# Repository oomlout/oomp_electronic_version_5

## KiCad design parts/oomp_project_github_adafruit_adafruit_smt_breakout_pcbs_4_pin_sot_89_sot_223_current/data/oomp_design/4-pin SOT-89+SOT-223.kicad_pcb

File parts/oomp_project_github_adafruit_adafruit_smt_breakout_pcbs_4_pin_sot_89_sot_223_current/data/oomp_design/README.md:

# OOMP KiCad design copy

Open `4-pin SOT-89+SOT-223.kicad_pro` (or the `.kicad_pcb` / `.kicad_sch`) in KiCad. Local OOMP libraries are under `libraries/`. Original inputs are preserved in [../original/](../original/).

Only verified unchanged installed KiCad defaults were renamed. Modified, custom, unmatched and unavailable items remain unchanged. Soldering variants are never swapped during conversion. Existing pad coordinates, nets and UUIDs are preserved.

See [conversion_report.yaml](conversion_report.yaml) for every conversion and skip. Copy this directory before editing; regeneration refuses to overwrite edited design files.

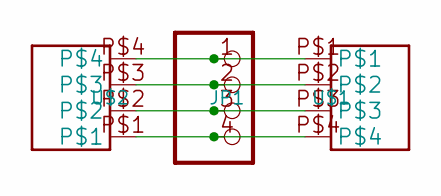
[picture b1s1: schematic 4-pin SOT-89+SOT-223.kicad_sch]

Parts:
JP1: PADS-4
U$1: SOT89
U$2: SOT223

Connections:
unnamed: JP1.1, U$1.P$1, U$2.P$4
unnamed: JP1.2, U$1.P$2, U$2.P$3
unnamed: JP1.3, U$1.P$3, U$2.P$2
unnamed: JP1.4, U$1.P$4, U$2.P$1

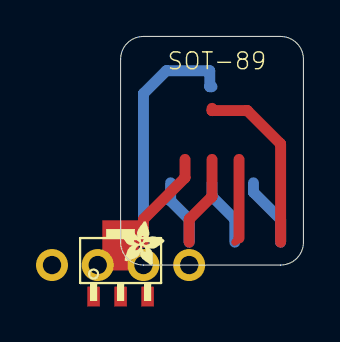
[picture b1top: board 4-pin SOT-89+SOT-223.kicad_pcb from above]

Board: 2 copper layers, 10.2 x 12.7 mm, 4 parts (1 on the bottom side), 4 nets.

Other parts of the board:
U$3: ADAFRUIT_2.5MM

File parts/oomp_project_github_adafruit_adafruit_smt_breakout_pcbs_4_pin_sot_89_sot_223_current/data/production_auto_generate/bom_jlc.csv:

Comment,Designator,Footprint,LCSC Part #
,U$3,4-pin SOT-89+SOT-223-import-fps:ADAFRUIT_2.5MM,
,JP1,4-pin SOT-89+SOT-223-import-fps:PADS-4,
SOT223,U$2,4-pin SOT-89+SOT-223-import-fps:SOT223,
SOT89,U$1,4-pin SOT-89+SOT-223-import-fps:SOT89,

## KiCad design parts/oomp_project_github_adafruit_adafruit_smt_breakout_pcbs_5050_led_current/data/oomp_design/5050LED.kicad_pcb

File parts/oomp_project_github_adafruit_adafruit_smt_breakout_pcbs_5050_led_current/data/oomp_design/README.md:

# OOMP KiCad design copy

Open `5050LED.kicad_pro` (or the `.kicad_pcb` / `.kicad_sch`) in KiCad. Local OOMP libraries are under `libraries/`. Original inputs are preserved in [../original/](../original/).

Only verified unchanged installed KiCad defaults were renamed. Modified, custom, unmatched and unavailable items remain unchanged. Soldering variants are never swapped during conversion. Existing pad coordinates, nets and UUIDs are preserved.

See [conversion_report.yaml](conversion_report.yaml) for every conversion and skip. Copy this directory before editing; regeneration refuses to overwrite edited design files.

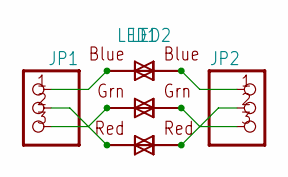
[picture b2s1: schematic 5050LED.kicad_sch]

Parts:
JP1, JP2: PINHD-1X3CB; 1X03-CLEANBIG
LED1, LED2: RGBLED5050

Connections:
unnamed: JP1.1, LED1.3 (BLUE_A), LED2.4 (BLUE_C)
unnamed: JP1.2, LED1.2 (RED_A), LED2.5 (RED_C)
unnamed: JP1.3, LED1.1 (GREEN_A), LED2.6 (GREEN_C)
unnamed: JP2.1, LED1.4 (BLUE_C), LED2.3 (BLUE_A)
unnamed: JP2.2, LED1.5 (RED_C), LED2.2 (RED_A)
unnamed: JP2.3, LED1.6 (GREEN_C), LED2.1 (GREEN_A)

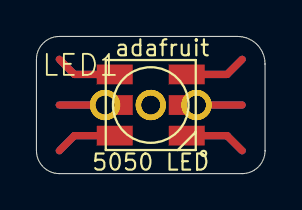
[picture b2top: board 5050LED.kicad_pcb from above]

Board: 2 copper layers, 12.7 x 7.6 mm, 4 parts (1 on the bottom side), 6 nets.

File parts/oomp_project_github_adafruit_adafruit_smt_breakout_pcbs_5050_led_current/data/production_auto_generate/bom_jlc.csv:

Comment,Designator,Footprint,LCSC Part #
,"JP1,JP2",5050LED-import-fps:1X03-CLEANBIG,C49257
RGBLED5050,"LED1,LED2",5050LED-import-fps:RGBLED5050,

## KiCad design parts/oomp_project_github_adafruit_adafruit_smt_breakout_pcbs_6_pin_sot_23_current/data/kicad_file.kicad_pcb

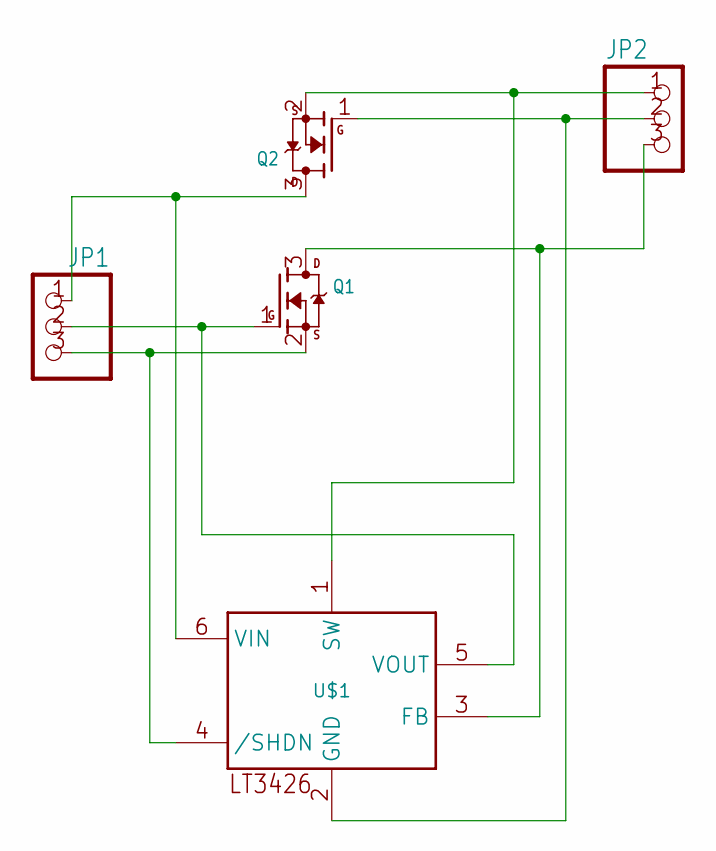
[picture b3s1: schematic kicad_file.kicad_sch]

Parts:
JP1, JP2: PINHD-1X3CB; 1X03-CLEANBIG
Q1, Q2: MOSFET-NREFLOW; SOT23
U$1: LT3426; SOT23-6

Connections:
GND: JP2.2, Q2.1 (G), U$1.2 (GND)
unnamed: JP2.3, Q1.3 (D), U$1.3 (FB)
unnamed: JP1.2, Q1.1 (G), U$1.5 (VOUT)
unnamed: JP1.3, Q1.2 (S), U$1.4 (/SHDN)
unnamed: JP2.1, Q2.2 (S), U$1.1 (SW)
unnamed: JP1.1, Q2.3 (D), U$1.6 (VIN)

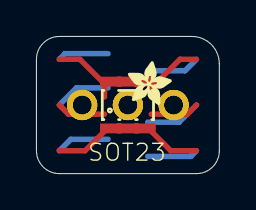
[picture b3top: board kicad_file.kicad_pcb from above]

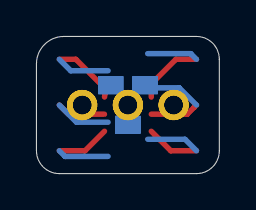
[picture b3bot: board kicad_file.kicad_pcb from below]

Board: 2 copper layers, 10.2 x 7.6 mm, 6 parts (2 on the bottom side), 6 nets.

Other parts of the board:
U$2: ADAFRUIT_2.5MM

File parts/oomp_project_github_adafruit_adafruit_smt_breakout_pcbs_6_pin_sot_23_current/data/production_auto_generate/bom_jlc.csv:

Comment,Designator,Footprint,LCSC Part #
,"JP1,JP2",6-pin SOT-23-import-fps:1X03-CLEANBIG,C49257
,U$2,6-pin SOT-23-import-fps:ADAFRUIT_2.5MM,
,"Q1,Q2",6-pin SOT-23-import-fps:SOT23,
LT3426,U$1,6-pin SOT-23-import-fps:SOT23-6,

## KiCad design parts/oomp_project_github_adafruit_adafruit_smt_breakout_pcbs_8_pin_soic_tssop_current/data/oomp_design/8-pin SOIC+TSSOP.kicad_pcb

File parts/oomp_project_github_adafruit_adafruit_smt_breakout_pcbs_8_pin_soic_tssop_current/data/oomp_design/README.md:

# OOMP KiCad design copy

Open `8-pin SOIC+TSSOP.kicad_pro` (or the `.kicad_pcb` / `.kicad_sch`) in KiCad. Local OOMP libraries are under `libraries/`. Original inputs are preserved in [../original/](../original/).

Only verified unchanged installed KiCad defaults were renamed. Modified, custom, unmatched and unavailable items remain unchanged. Soldering variants are never swapped during conversion. Existing pad coordinates, nets and UUIDs are preserved.

See [conversion_report.yaml](conversion_report.yaml) for every conversion and skip. Copy this directory before editing; regeneration refuses to overwrite edited design files.

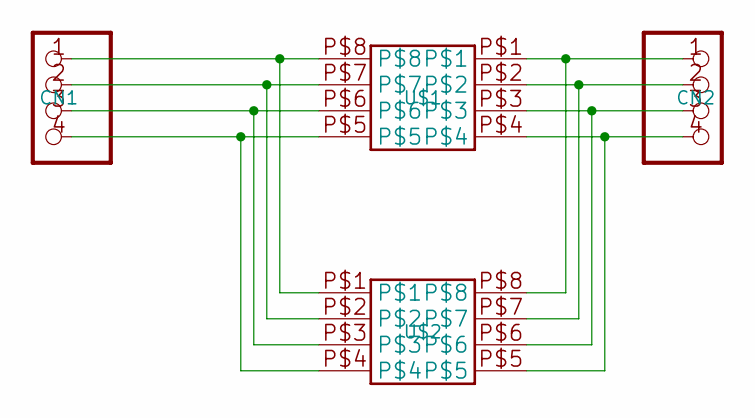
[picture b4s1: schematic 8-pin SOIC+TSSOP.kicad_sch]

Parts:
CN1, CN2: PADS-4
U$1: 8-PINSOIC-NW; SO8NW
U$2: 8-PINTSSOP; TSSOP8

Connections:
unnamed: CN1.1, U$1.P$8, U$2.P$1
unnamed: CN2.1, U$1.P$1, U$2.P$8
unnamed: CN2.2, U$1.P$2, U$2.P$7
unnamed: CN2.3, U$1.P$3, U$2.P$6
unnamed: CN2.4, U$1.P$4, U$2.P$5
unnamed: CN1.2, U$1.P$7, U$2.P$2
unnamed: CN1.3, U$1.P$6, U$2.P$3
unnamed: CN1.4, U$1.P$5, U$2.P$4

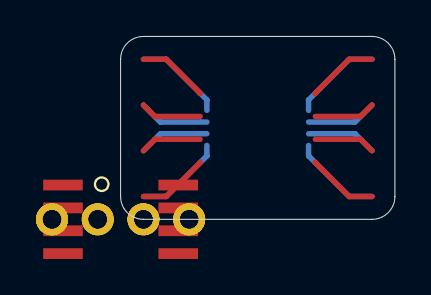
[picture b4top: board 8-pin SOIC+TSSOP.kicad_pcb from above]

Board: 2 copper layers, 15.2 x 10.2 mm, 4 parts (1 on the bottom side), 8 nets.

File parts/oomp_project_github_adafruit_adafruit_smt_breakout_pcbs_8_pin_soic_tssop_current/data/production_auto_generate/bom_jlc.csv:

Comment,Designator,Footprint,LCSC Part #
,"CN1,CN2",8-pin SOIC+TSSOP-import-fps:PADS-4,
8-PINSOIC-NW,U$1,8-pin SOIC+TSSOP-import-fps:SO8NW,
8-PINTSSOP,U$2,8-pin SOIC+TSSOP-import-fps:TSSOP8,
